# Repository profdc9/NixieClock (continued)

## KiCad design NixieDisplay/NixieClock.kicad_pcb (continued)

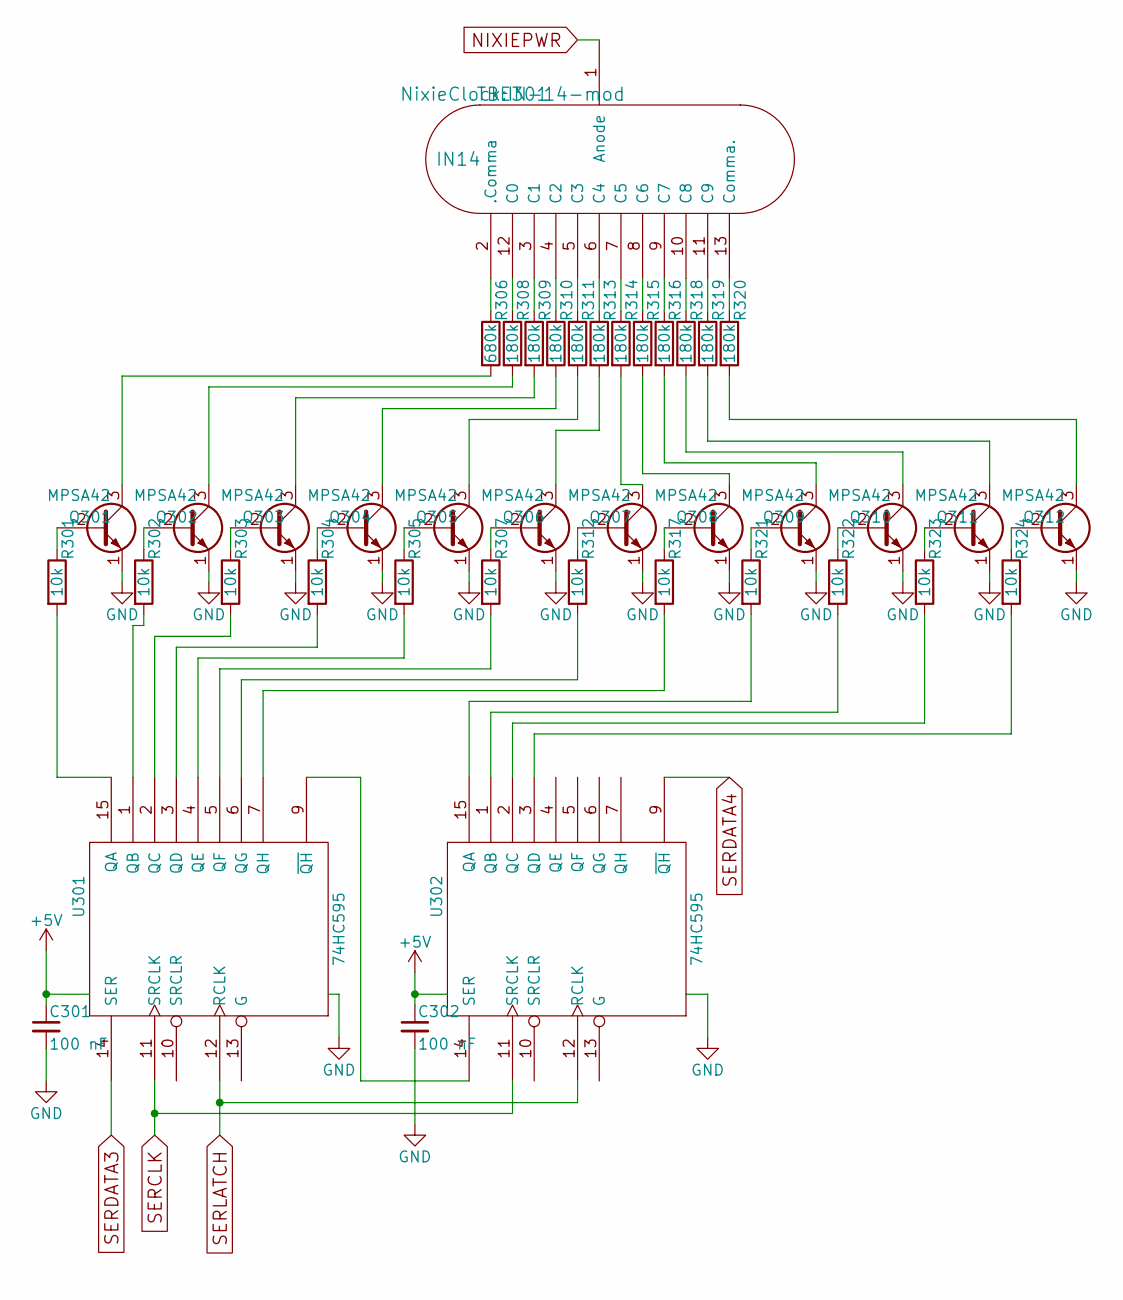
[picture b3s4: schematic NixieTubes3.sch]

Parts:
C301, C302: 100 nF; C_Disc_D5.0mm_W2.5mm_P2.50mm
Q301, Q302, Q303, Q304, Q305, Q306, Q307, Q308, Q309, Q310, Q311, Q312: MPSA42; TO-92_Molded_Narrow
R301, R302, R303, R304, R305, R307, R312, R317, R321, R322, R323, R324: 10k; R_Axial_DIN0207_L6.3mm_D2.5mm_P7.62mm_Horizontal
R306: 680k; R_Axial_DIN0207_L6.3mm_D2.5mm_P7.62mm_Horizontal
R308, R309, R310, R311, R313, R314, R315, R316, R318, R319, R320: 180k; R_Axial_DIN0207_L6.3mm_D2.5mm_P7.62mm_Horizontal
TBE301: IN14; IN-14-mod
U301, U302: 74HC595; DIP-16_W7.62mm_Socket

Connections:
+5V: C301.1, C302.1, U301.16 (VCC), U302.16 (VCC); also elsewhere on the board
GND: C301.2, C302.2, Q301.1 (E), Q302.1 (E), Q303.1 (E), Q304.1 (E), Q305.1 (E), Q306.1 (E), Q307.1 (E), Q308.1 (E), Q309.1 (E), Q310.1 (E), Q311.1 (E), Q312.1 (E), U301.8 (GND), U302.8 (GND); also elsewhere on the board
NIXIEPWR: TBE301.1 (Anode); also elsewhere on the board
unnamed: Q301.2 (B), R301.1
unnamed: Q301.3 (C), R306.2
unnamed: Q302.2 (B), R302.1
unnamed: Q302.3 (C), R308.2
unnamed: Q303.2 (B), R303.1
unnamed: Q303.3 (C), R309.2
unnamed: Q304.2 (B), R304.1
unnamed: Q304.3 (C), R310.2
unnamed: Q305.2 (B), R305.1
unnamed: Q305.3 (C), R311.2
unnamed: Q306.2 (B), R307.1
unnamed: Q306.3 (C), R313.2
unnamed: Q307.2 (B), R312.1
unnamed: Q307.3 (C), R314.2
unnamed: Q308.2 (B), R317.1
unnamed: Q308.3 (C), R315.2
unnamed: Q309.2 (B), R321.1
unnamed: Q309.3 (C), R316.2
unnamed: Q310.2 (B), R322.1
unnamed: Q310.3 (C), R318.2
unnamed: Q311.2 (B), R323.1
unnamed: Q311.3 (C), R319.2
unnamed: Q312.2 (B), R324.1
unnamed: Q312.3 (C), R320.2
unnamed: R301.2, U301.15 (QA)
unnamed: R302.2, U301.1 (QB)
unnamed: R303.2, U301.2 (QC)
unnamed: R304.2, U301.3 (QD)
unnamed: R305.2, U301.4 (QE)
unnamed: R306.1, TBE301.2 (.Comma)
unnamed: R307.2, U301.5 (QF)
unnamed: R308.1, TBE301.12 (C0)
unnamed: R309.1, TBE301.3 (C1)
unnamed: R310.1, TBE301.4 (C2)
unnamed: R311.1, TBE301.5 (C3)
unnamed: R312.2, U301.6 (QG)
unnamed: R313.1, TBE301.6 (C4)
unnamed: R314.1, TBE301.7 (C5)
unnamed: R315.1, TBE301.8 (C6)
unnamed: R316.1, TBE301.9 (C7)
unnamed: R317.2, U301.7 (QH)
unnamed: R318.1, TBE301.10 (C8)
unnamed: R319.1, TBE301.11 (C9)
unnamed: R320.1, TBE301.13 (Comma.)
unnamed: R321.2, U302.15 (QA)
unnamed: R322.2, U302.1 (QB)
unnamed: R323.2, U302.2 (QC)
unnamed: R324.2, U302.3 (QD)
unnamed: U301.9 (~QH), U302.14 (SER)
SERCLK: U301.11 (SRCLK), U302.11 (SRCLK); also elsewhere on the board
SERDATA3: U301.14 (SER); also elsewhere on the board
SERDATA4: U302.9 (~QH); also elsewhere on the board
SERLATCH: U301.12 (RCLK), U302.12 (RCLK); also elsewhere on the board

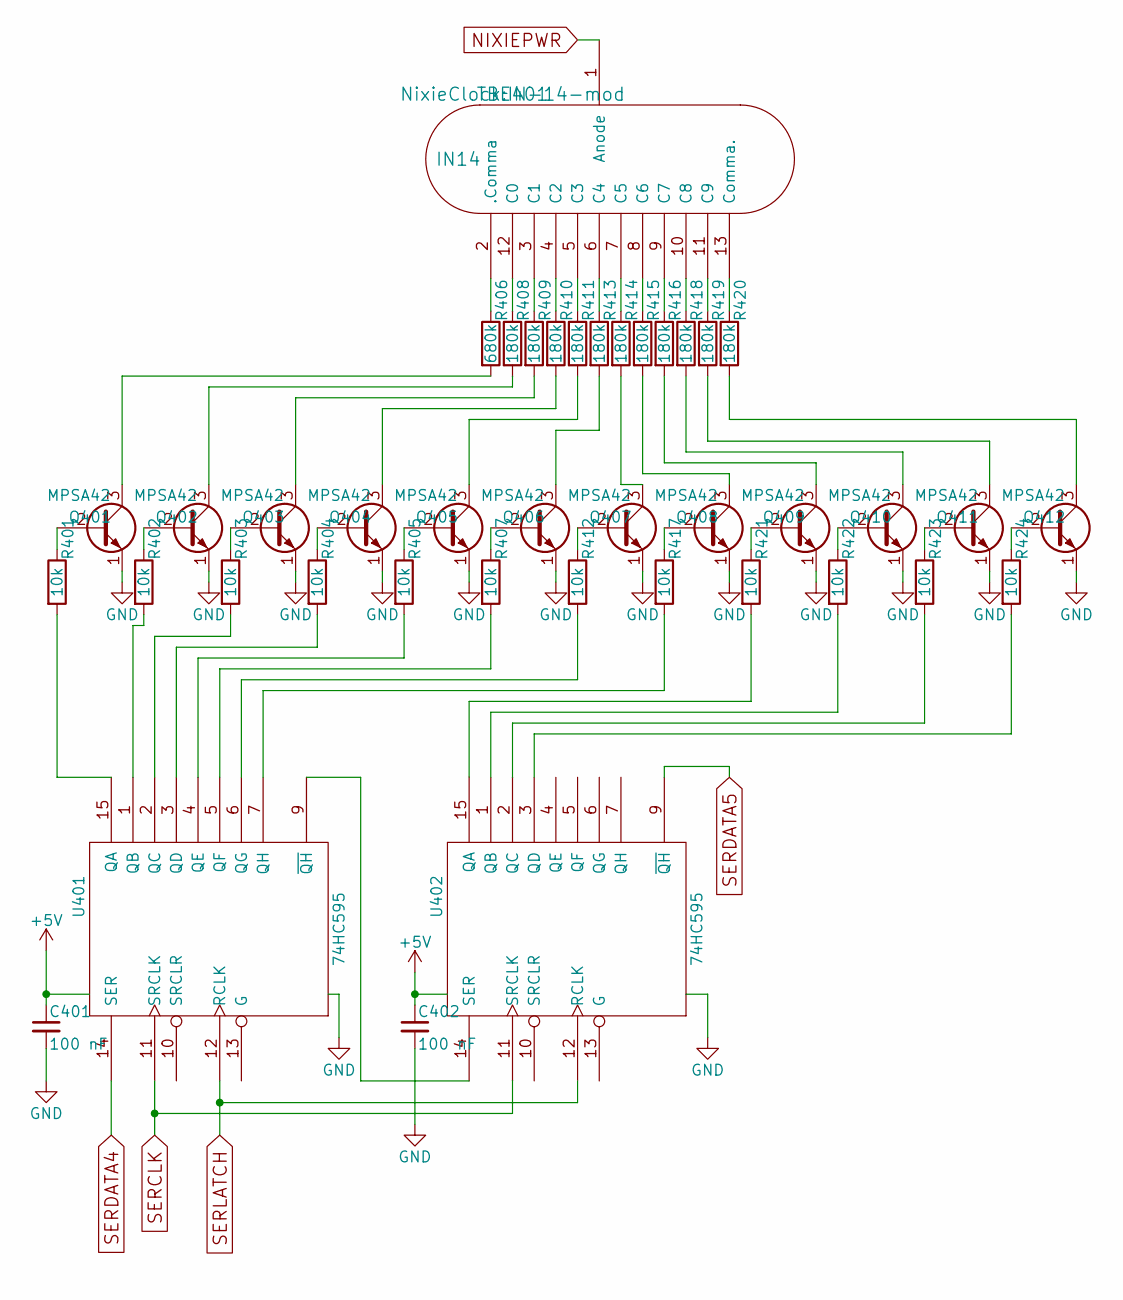
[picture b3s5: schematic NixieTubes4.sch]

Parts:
C401, C402: 100 nF; C_Disc_D5.0mm_W2.5mm_P2.50mm
Q401, Q402, Q403, Q404, Q405, Q406, Q407, Q408, Q409, Q410, Q411, Q412: MPSA42; TO-92_Molded_Narrow
R401, R402, R403, R404, R405, R407, R412, R417, R421, R422, R423, R424: 10k; R_Axial_DIN0207_L6.3mm_D2.5mm_P7.62mm_Horizontal
R406: 680k; R_Axial_DIN0207_L6.3mm_D2.5mm_P7.62mm_Horizontal
R408, R409, R410, R411, R413, R414, R415, R416, R418, R419, R420: 180k; R_Axial_DIN0207_L6.3mm_D2.5mm_P7.62mm_Horizontal
TBE401: IN14; IN-14-mod
U401, U402: 74HC595; DIP-16_W7.62mm_Socket

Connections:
+5V: C401.1, C402.1, U401.16 (VCC), U402.16 (VCC); also elsewhere on the board
GND: C401.2, C402.2, Q401.1 (E), Q402.1 (E), Q403.1 (E), Q404.1 (E), Q405.1 (E), Q406.1 (E), Q407.1 (E), Q408.1 (E), Q409.1 (E), Q410.1 (E), Q411.1 (E), Q412.1 (E), U401.8 (GND), U402.8 (GND); also elsewhere on the board
NIXIEPWR: TBE401.1 (Anode); also elsewhere on the board
unnamed: Q401.2 (B), R401.1
unnamed: Q401.3 (C), R406.2
unnamed: Q402.2 (B), R402.1
unnamed: Q402.3 (C), R408.2
unnamed: Q403.2 (B), R403.1
unnamed: Q403.3 (C), R409.2
unnamed: Q404.2 (B), R404.1
unnamed: Q404.3 (C), R410.2
unnamed: Q405.2 (B), R405.1
unnamed: Q405.3 (C), R411.2
unnamed: Q406.2 (B), R407.1
unnamed: Q406.3 (C), R413.2
unnamed: Q407.2 (B), R412.1
unnamed: Q407.3 (C), R414.2
unnamed: Q408.2 (B), R417.1
unnamed: Q408.3 (C), R415.2
unnamed: Q409.2 (B), R421.1
unnamed: Q409.3 (C), R416.2
unnamed: Q410.2 (B), R422.1
unnamed: Q410.3 (C), R418.2
unnamed: Q411.2 (B), R423.1
unnamed: Q411.3 (C), R419.2
unnamed: Q412.2 (B), R424.1
unnamed: Q412.3 (C), R420.2
unnamed: R401.2, U401.15 (QA)
unnamed: R402.2, U401.1 (QB)
unnamed: R403.2, U401.2 (QC)
unnamed: R404.2, U401.3 (QD)
unnamed: R405.2, U401.4 (QE)
unnamed: R406.1, TBE401.2 (.Comma)
unnamed: R407.2, U401.5 (QF)
unnamed: R408.1, TBE401.12 (C0)
unnamed: R409.1, TBE401.3 (C1)
unnamed: R410.1, TBE401.4 (C2)
unnamed: R411.1, TBE401.5 (C3)
unnamed: R412.2, U401.6 (QG)
unnamed: R413.1, TBE401.6 (C4)
unnamed: R414.1, TBE401.7 (C5)
unnamed: R415.1, TBE401.8 (C6)
unnamed: R416.1, TBE401.9 (C7)
unnamed: R417.2, U401.7 (QH)
unnamed: R418.1, TBE401.10 (C8)
unnamed: R419.1, TBE401.11 (C9)
unnamed: R420.1, TBE401.13 (Comma.)
unnamed: R421.2, U402.15 (QA)
unnamed: R422.2, U402.1 (QB)
unnamed: R423.2, U402.2 (QC)
unnamed: R424.2, U402.3 (QD)
unnamed: U401.9 (~QH), U402.14 (SER)
SERCLK: U401.11 (SRCLK), U402.11 (SRCLK); also elsewhere on the board
SERDATA4: U401.14 (SER); also elsewhere on the board
SERDATA5: U402.9 (~QH); also elsewhere on the board
SERLATCH: U401.12 (RCLK), U402.12 (RCLK); also elsewhere on the board

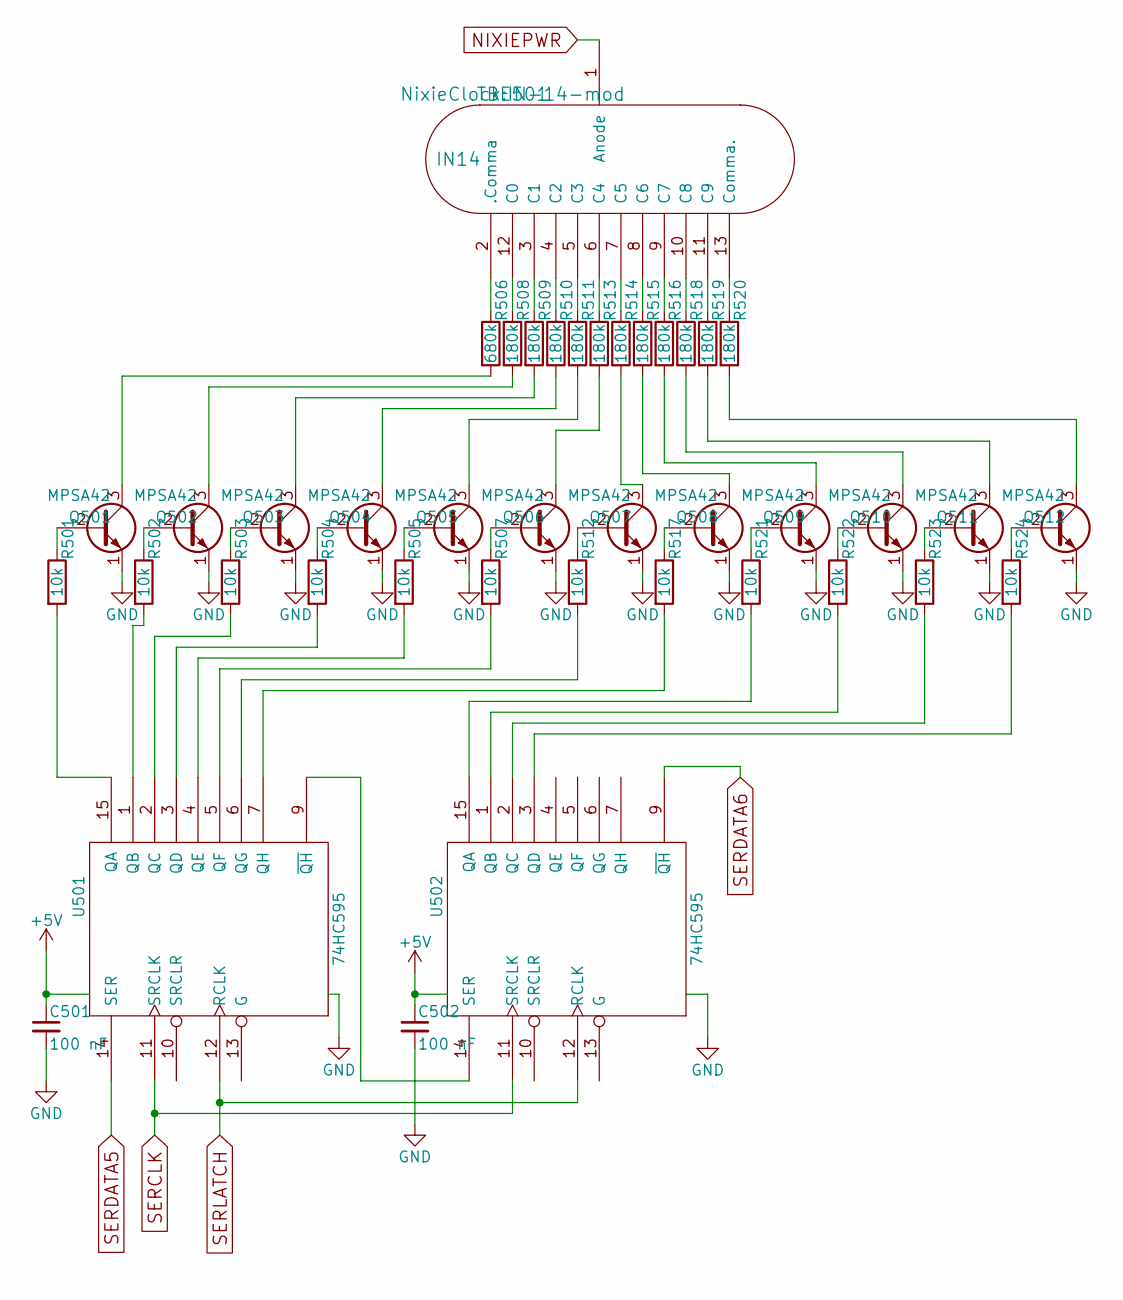
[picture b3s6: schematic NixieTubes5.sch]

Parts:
C501, C502: 100 nF; C_Disc_D5.0mm_W2.5mm_P2.50mm
Q501, Q502, Q503, Q504, Q505, Q506, Q507, Q508, Q509, Q510, Q511, Q512: MPSA42; TO-92_Molded_Narrow
R501, R502, R503, R504, R505, R507, R512, R517, R521, R522, R523, R524: 10k; R_Axial_DIN0207_L6.3mm_D2.5mm_P7.62mm_Horizontal
R506: 680k; R_Axial_DIN0207_L6.3mm_D2.5mm_P7.62mm_Horizontal
R508, R509, R510, R511, R513, R514, R515, R516, R518, R519, R520: 180k; R_Axial_DIN0207_L6.3mm_D2.5mm_P7.62mm_Horizontal
TBE501: IN14; IN-14-mod
U501, U502: 74HC595; DIP-16_W7.62mm_Socket

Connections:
+5V: C501.1, C502.1, U501.16 (VCC), U502.16 (VCC); also elsewhere on the board
GND: C501.2, C502.2, Q501.1 (E), Q502.1 (E), Q503.1 (E), Q504.1 (E), Q505.1 (E), Q506.1 (E), Q507.1 (E), Q508.1 (E), Q509.1 (E), Q510.1 (E), Q511.1 (E), Q512.1 (E), U501.8 (GND), U502.8 (GND); also elsewhere on the board
NIXIEPWR: TBE501.1 (Anode); also elsewhere on the board
unnamed: Q501.2 (B), R501.1
unnamed: Q501.3 (C), R506.2
unnamed: Q502.2 (B), R502.1
unnamed: Q502.3 (C), R508.2
unnamed: Q503.2 (B), R503.1
unnamed: Q503.3 (C), R509.2
unnamed: Q504.2 (B), R504.1
unnamed: Q504.3 (C), R510.2
unnamed: Q505.2 (B), R505.1
unnamed: Q505.3 (C), R511.2
unnamed: Q506.2 (B), R507.1
unnamed: Q506.3 (C), R513.2
unnamed: Q507.2 (B), R512.1
unnamed: Q507.3 (C), R514.2
unnamed: Q508.2 (B), R517.1
unnamed: Q508.3 (C), R515.2
unnamed: Q509.2 (B), R521.1
unnamed: Q509.3 (C), R516.2
unnamed: Q510.2 (B), R522.1
unnamed: Q510.3 (C), R518.2
unnamed: Q511.2 (B), R523.1
unnamed: Q511.3 (C), R519.2
unnamed: Q512.2 (B), R524.1
unnamed: Q512.3 (C), R520.2
unnamed: R501.2, U501.15 (QA)
unnamed: R502.2, U501.1 (QB)
unnamed: R503.2, U501.2 (QC)
unnamed: R504.2, U501.3 (QD)
unnamed: R505.2, U501.4 (QE)
unnamed: R506.1, TBE501.2 (.Comma)
unnamed: R507.2, U501.5 (QF)
unnamed: R508.1, TBE501.12 (C0)
unnamed: R509.1, TBE501.3 (C1)
unnamed: R510.1, TBE501.4 (C2)
unnamed: R511.1, TBE501.5 (C3)
unnamed: R512.2, U501.6 (QG)
unnamed: R513.1, TBE501.6 (C4)
unnamed: R514.1, TBE501.7 (C5)
unnamed: R515.1, TBE501.8 (C6)
unnamed: R516.1, TBE501.9 (C7)
unnamed: R517.2, U501.7 (QH)
unnamed: R518.1, TBE501.10 (C8)
unnamed: R519.1, TBE501.11 (C9)
unnamed: R520.1, TBE501.13 (Comma.)
unnamed: R521.2, U502.15 (QA)
unnamed: R522.2, U502.1 (QB)
unnamed: R523.2, U502.2 (QC)
unnamed: R524.2, U502.3 (QD)
unnamed: U501.9 (~QH), U502.14 (SER)
SERCLK: U501.11 (SRCLK), U502.11 (SRCLK); also elsewhere on the board
SERDATA5: U501.14 (SER); also elsewhere on the board
SERDATA6: U502.9 (~QH); also elsewhere on the board
SERLATCH: U501.12 (RCLK), U502.12 (RCLK); also elsewhere on the board

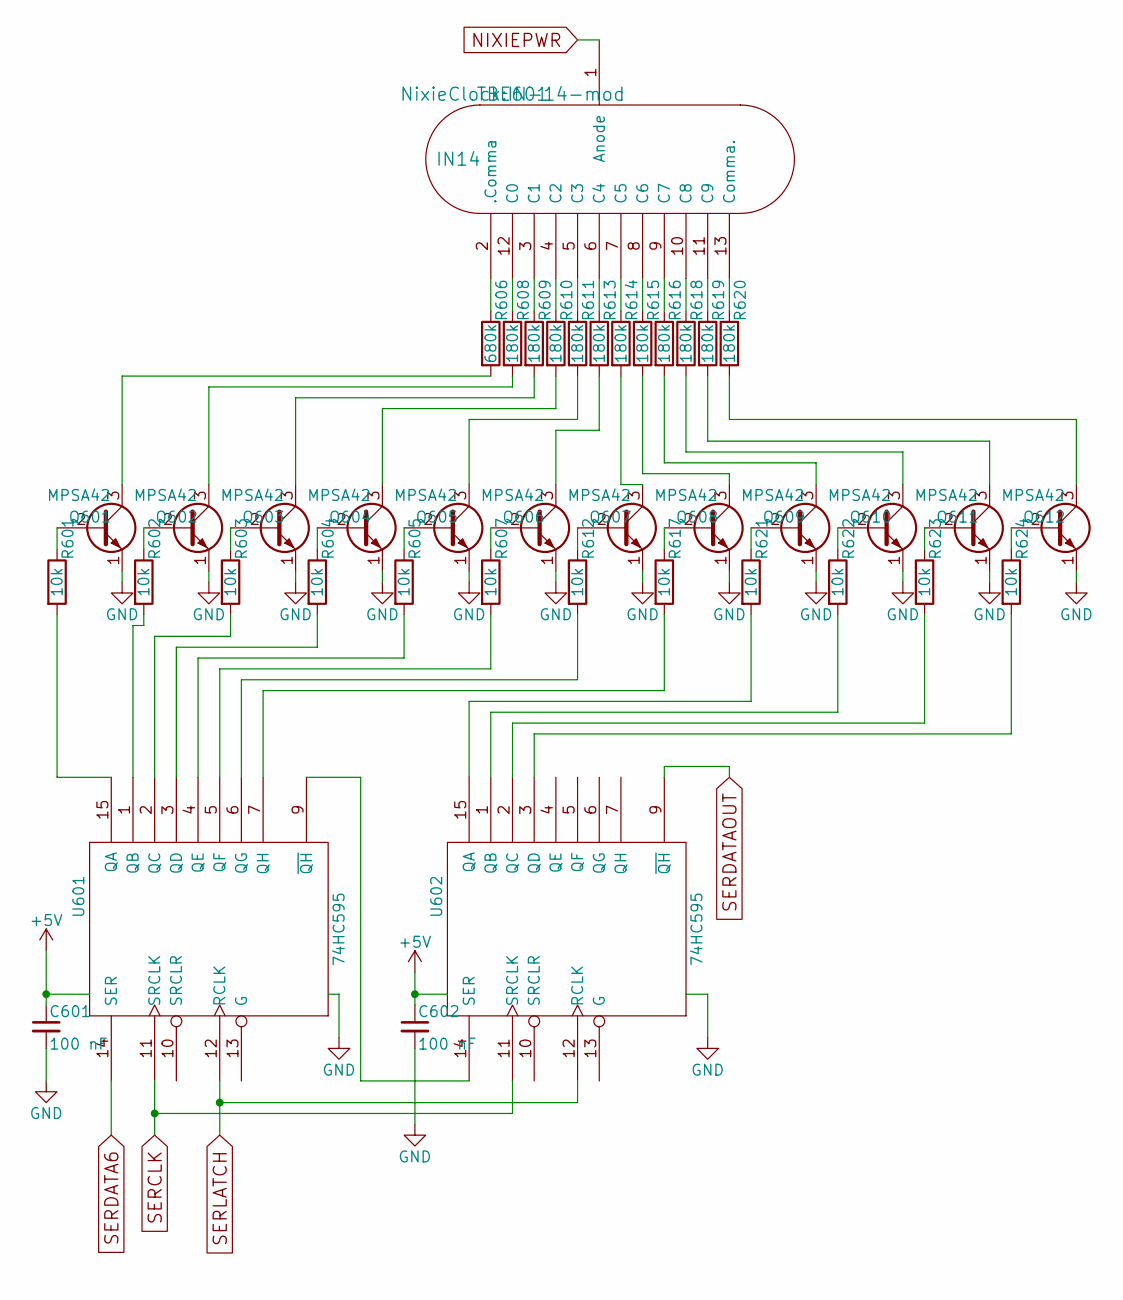
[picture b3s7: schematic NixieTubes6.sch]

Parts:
C601, C602: 100 nF; C_Disc_D5.0mm_W2.5mm_P2.50mm
Q601, Q602, Q603, Q604, Q605, Q606, Q607, Q608, Q609, Q610, Q611, Q612: MPSA42; TO-92_Molded_Narrow
R601, R602, R603, R604, R605, R607, R612, R617, R621, R622, R623, R624: 10k; R_Axial_DIN0207_L6.3mm_D2.5mm_P7.62mm_Horizontal
R606: 680k; R_Axial_DIN0207_L6.3mm_D2.5mm_P7.62mm_Horizontal
R608, R609, R610, R611, R613, R614, R615, R616, R618, R619, R620: 180k; R_Axial_DIN0207_L6.3mm_D2.5mm_P7.62mm_Horizontal
TBE601: IN14; IN-14-mod
U601, U602: 74HC595; DIP-16_W7.62mm_Socket

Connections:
+5V: C601.1, C602.1, U601.16 (VCC), U602.16 (VCC); also elsewhere on the board
GND: C601.2, C602.2, Q601.1 (E), Q602.1 (E), Q603.1 (E), Q604.1 (E), Q605.1 (E), Q606.1 (E), Q607.1 (E), Q608.1 (E), Q609.1 (E), Q610.1 (E), Q611.1 (E), Q612.1 (E), U601.8 (GND), U602.8 (GND); also elsewhere on the board
NIXIEPWR: TBE601.1 (Anode); also elsewhere on the board
unnamed: Q601.2 (B), R601.1
unnamed: Q601.3 (C), R606.2
unnamed: Q602.2 (B), R602.1
unnamed: Q602.3 (C), R608.2
unnamed: Q603.2 (B), R603.1
unnamed: Q603.3 (C), R609.2
unnamed: Q604.2 (B), R604.1
unnamed: Q604.3 (C), R610.2
unnamed: Q605.2 (B), R605.1
unnamed: Q605.3 (C), R611.2
unnamed: Q606.2 (B), R607.1
unnamed: Q606.3 (C), R613.2
unnamed: Q607.2 (B), R612.1
unnamed: Q607.3 (C), R614.2
unnamed: Q608.2 (B), R617.1
unnamed: Q608.3 (C), R615.2
unnamed: Q609.2 (B), R621.1
unnamed: Q609.3 (C), R616.2
unnamed: Q610.2 (B), R622.1
unnamed: Q610.3 (C), R618.2
unnamed: Q611.2 (B), R623.1
unnamed: Q611.3 (C), R619.2
unnamed: Q612.2 (B), R624.1
unnamed: Q612.3 (C), R620.2
unnamed: R601.2, U601.15 (QA)
unnamed: R602.2, U601.1 (QB)
unnamed: R603.2, U601.2 (QC)
unnamed: R604.2, U601.3 (QD)
unnamed: R605.2, U601.4 (QE)
unnamed: R606.1, TBE601.2 (.Comma)
unnamed: R607.2, U601.5 (QF)
unnamed: R608.1, TBE601.12 (C0)
unnamed: R609.1, TBE601.3 (C1)
unnamed: R610.1, TBE601.4 (C2)
unnamed: R611.1, TBE601.5 (C3)
unnamed: R612.2, U601.6 (QG)
unnamed: R613.1, TBE601.6 (C4)
unnamed: R614.1, TBE601.7 (C5)
unnamed: R615.1, TBE601.8 (C6)
unnamed: R616.1, TBE601.9 (C7)
unnamed: R617.2, U601.7 (QH)
unnamed: R618.1, TBE601.10 (C8)
unnamed: R619.1, TBE601.11 (C9)
unnamed: R620.1, TBE601.13 (Comma.)
unnamed: R621.2, U602.15 (QA)
unnamed: R622.2, U602.1 (QB)
unnamed: R623.2, U602.2 (QC)
unnamed: R624.2, U602.3 (QD)
unnamed: U601.9 (~QH), U602.14 (SER)
SERCLK: U601.11 (SRCLK), U602.11 (SRCLK); also elsewhere on the board
SERDATA6: U601.14 (SER); also elsewhere on the board
SERDATAOUT: U602.9 (~QH); also elsewhere on the board
SERLATCH: U601.12 (RCLK), U602.12 (RCLK); also elsewhere on the board

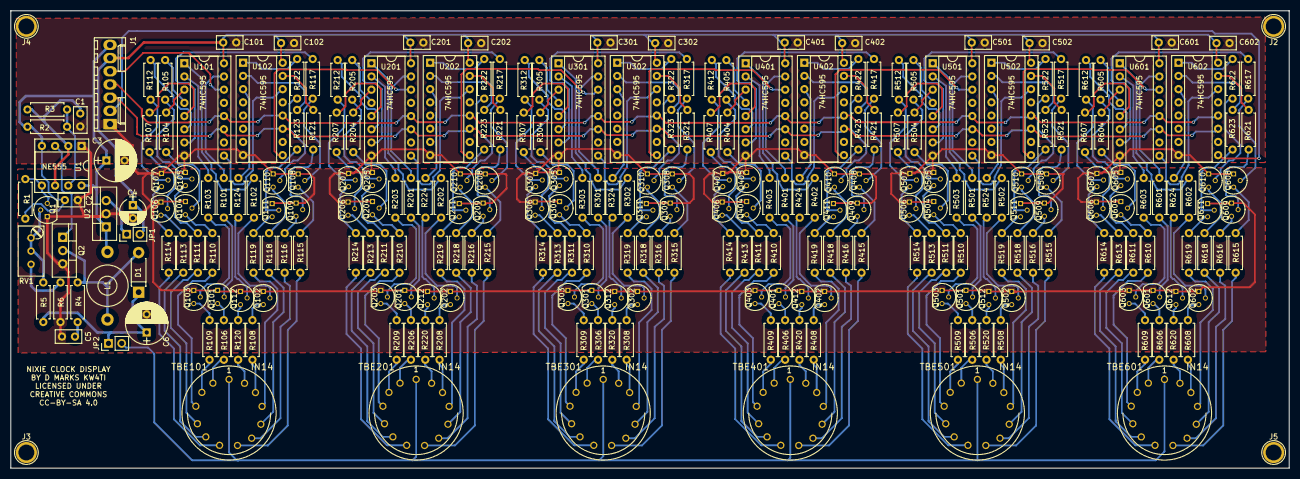
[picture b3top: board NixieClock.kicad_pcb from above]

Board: 2 copper layers, 246.0 x 88.0 mm, 272 parts (0 on the bottom side), 317 nets.

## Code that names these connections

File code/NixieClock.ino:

/*  NixieClock.ino */

/*
 * Copyright (c) 2020 Daniel Marks

This software is provided 'as-is', without any express or implied
warranty. In no event will the authors be held liable for any damages
arising from the use of this software.

Permission is granted to anyone to use this software for any purpose,
including commercial applications, and to alter it and redistribute it
freely, subject to the following restrictions:

1. The origin of this software must not be misrepresented; you must not
   claim that you wrote the original software. If you use this software
   in a product, an acknowledgment in the product documentation would be
   appreciated but is not required.
2. Altered source versions must be plainly marked as such, and must not be
   misrepresented as being the original software.
3. This notice may not be removed or altered from any source distribution.
 */

 #define DHT_SENSOR

#include <Arduino.h>
#include <SPI.h>
#include <Wire.h>
#include <EEPROM.h>
#include <DS3231.h>

#ifdef DHT_SENSOR
#include <DHT.h>
#endif

#define SERIAL_LATCH 10
#define SERIAL_DATA 11
#define SERIAL_DATAOUT 12
#define SERIAL_CLK 13
#define BUTTON1 14
#define BUTTON2 15
#define BUTTON3 16

#define ARDUINORX 1
#define ARDUINOTX 0

#define I2C_SDA 4
#define I2C_SCL 5

#define LED1 3
#define LED2 5
#define LED3 6

#define EEPROM_1224HR 0
#define EEPROM_TEMPCF 1

SPISettings spiA(4000000, MSBFIRST, SPI_MODE0);

#define NUM_DIGITS 6

const byte digit_code[] =   { 0x01, 0x02, 0x04, 0x08, 0x10, 0x20 };
const byte number1_code[] = { 0x00, 0x04, 0x08, 0x10, 0x20, 0x40, 0x80, 0x01, 0x00, 0x00, 0x02, 0x00, 0x00 };
const byte number2_code[] = { 0x04, 0x00, 0x00, 0x00, 0x00, 0x00, 0x00, 0x00, 0x01, 0x02, 0x00, 0x08, 0x00 };

const byte ticks1_code[] = { 0x00, 0x00, 0x02, 0x02 };
const byte ticks2_code[] = { 0x00, 0x08, 0x00, 0x08 };

volatile byte digits[NUM_DIGITS];
volatile byte ticks[NUM_DIGITS];
byte displayrefreshcycles;
byte current_digit;
byte hour12;
byte tempcf;
DS3231 Clock;
#ifdef DHT_SENSOR
DHT DHTSensor(4, DHT22, 1);
#endif

#define NUM_BUTTONS 3

const byte buttonPin[NUM_BUTTONS] = {BUTTON1, BUTTON2, BUTTON3};
static byte constStateButton[NUM_BUTTONS];
volatile byte curStateButton[NUM_BUTTONS];
volatile bool pushedButton[NUM_BUTTONS];

void write_led_state(byte d1, byte d2, byte d3)
{
  analogWrite(LED1,d1);
  analogWrite(LED2,d2);
  analogWrite(LED3,d3);
}

bool isButtonDown(byte b)
{
  return !curStateButton[b];
}

void waitButtonUp(byte b)
{
  while (curStateButton[b] == LOW);
  pushedButton[b] = false;
}

bool getPushedButton(byte b)
{
  if (pushedButton[b])
  {
    pushedButton[b] = false;
    return true;
  }
  return false;
}

void debounce_buttons(void)
{
  for (byte b = 0; b < NUM_BUTTONS; b++)
  {
    byte state = digitalRead(buttonPin[b]);
    if (curStateButton[b] != state)
    {
      if ((++constStateButton[b]) >= 50)
      {
        curStateButton[b] = state;
        if (state == LOW) pushedButton[b] = true;
        constStateButton[b] = 0;
      }
    } else constStateButton[b] = 0;
  }
}

ISR(TIMER1_COMPA_vect)
{
  SPI.beginTransaction(spiA);
  if (displayrefreshcycles > 0)
  {
    displayrefreshcycles--;
    SPI.transfer(digit_code[current_digit]);
    SPI.transfer(number2_code[digits[current_digit]] | ticks2_code[ticks[current_digit]] );
    SPI.transfer(number1_code[digits[current_digit]] | ticks1_code[ticks[current_digit]] );
  }
  else
  {
    displayrefreshcycles = 4;
    SPI.transfer(0);
    SPI.transfer(0);
    SPI.transfer(0);
    if ((++current_digit) >= NUM_DIGITS)
      current_digit = 0;
  }
  SPI.endTransaction();
  digitalWrite(SERIAL_LATCH, LOW);
  debounce_buttons();
  digitalWrite(SERIAL_LATCH, HIGH);
}

void setup() {
  current_digit = 0;
  pinMode(SERIAL_LATCH, OUTPUT);
  pinMode(LED1, OUTPUT);
  digitalWrite(LED1, LOW);
  pinMode(LED2, OUTPUT);
  digitalWrite(LED2, LOW);
  pinMode(LED3, OUTPUT);
  digitalWrite(LED3, LOW);
  pinMode(BUTTON1, INPUT);
  pinMode(BUTTON2, INPUT);
  pinMode(BUTTON3, INPUT);
  SPI.begin();

  noInterrupts();           // disable all interrupts
  TCCR1A = 0;
  TCCR1B = 0;
  TCNT1  = 0;
  OCR1A = 16;            // compare match register 16MHz/256/2Hz
  TCCR1B |= (1 << WGM12);   // CTC mode
  TCCR1B |= ((1 << CS11) | (1 << CS10));    // 256 prescaler
  TIMSK1 |= (1 << OCIE1A);  // enable timer compare interrupt
  interrupts();             // enable all interrupts

  Serial.begin(9600);
  Wire.begin();
  Clock.setClockMode(false);
  hour12 = (EEPROM.read(EEPROM_1224HR) == 1) ? 1 : 0;
  tempcf = (EEPROM.read(EEPROM_TEMPCF) == 1) ? 1 : 0;
#ifdef DHT_SENSOR
  DHTSensor.begin();
#endif
}

void display_1_number(byte ind, byte b)
{
  digits[ind] = b / 10;
  digits[ind + 1] = b % 10;
}

void display_three_numbers(byte n1, byte n2, byte n3)
{
  display_1_number(0, n1);
  display_1_number(2, n2);
  display_1_number(4, n3);
}

void display_current_time(void)
{
  bool h12, PM;
  byte nowHour = Clock.getHour(h12, PM);
  if (hour12)
  {
    if ((nowHour >= 12) && (nowHour <= 23)) ticks[0] = ticks[1] = 1;
    if (nowHour > 12) nowHour -= 12;
    if (nowHour == 0) nowHour = 12;
  }
  display_three_numbers(nowHour, Clock.getMinute(), Clock.getSecond());
}

void display_current_date(void)
{
  bool Century;
  display_three_numbers(Clock.getYear(), Clock.getMonth(Century), Clock.getDate());
}

void set_digs(byte *v, byte val)
{
  for (byte i = 0; i < NUM_DIGITS; i++) v[i] = val;
}

void clear_display(void)
{
  set_digs(digits, 12);
}

void clear_ticks(void)
{
  set_digs(ticks, 0);
}

void all_ticks(void)
{
  set_digs(ticks, 3);
}

unsigned short getNewNumber(unsigned short n, byte dig, byte ndig, unsigned short minval, unsigned short maxval)
{
  clear_ticks();
  for (;;)
  {
    unsigned short v = n;
    for (byte i = ndig; i > 0;)
    {
      i--;
      digits[dig + i] = v % 10;
      ticks[dig + i] = 3;
      v = v / 10;
    }
    if (getPushedButton(2))
    {
      if (n > minval) n--;
      else n = maxval;
    } else if (getPushedButton(1))
    {
      if (n < maxval) n++;
      else n = minval;
    } else if (getPushedButton(0))
      break;
  }
  return n;
}

void set_time_and_date(void)
{
  bool h12, PM, Century;
  clear_display();
  delay(500);
  hour12 = getNewNumber(hour12, 0, 1, 0, 1);
  EEPROM.write(EEPROM_1224HR, hour12);
#ifdef DHT_SENSOR
  clear_display();
  tempcf = getNewNumber(tempcf, 1, 2, 0, 1);
  EEPROM.write(EEPROM_TEMPCF, tempcf);
#endif
  display_three_numbers(Clock.getYear(), Clock.getMonth(Century), Clock.getDate());
  byte newYear = getNewNumber(Clock.getYear(), 0, 2, 0, 99);
  byte newMonth = getNewNumber(Clock.getMonth(Century), 2, 2, 1, 12);
  byte newDate = getNewNumber(Clock.getDate(), 4, 2, 1, 31);
  display_current_time();
  byte newHour = Clock.getHour(h12, PM);
  newHour = getNewNumber(newHour, 0, 2, 0, 23);
  byte newMinute = getNewNumber(Clock.getMinute(), 2, 2, 0, 59);
  byte newSecond = getNewNumber(Clock.getSecond(), 4, 2, 0, 59);
  Clock.setYear(newYear);
  Clock.setMonth(newMonth);
  Clock.setDate(newDate);
  Clock.setHour(newHour);
  Clock.setMinute(newMinute);
  Clock.setSecond(newSecond);
  all_ticks();
  delay(1000);
}

void cathode_condition()
{
  clear_ticks();
  for (byte i = 0; i < 12; i++)
  {
    set_digs(digits, i);
    for (byte j = 0; j < 240; j++)
    {
      delay(250);
      if (getPushedButton(0)) break;
      if (getPushedButton(2)) return;
    }
  }
}

#ifdef DHT_SENSOR
void display_dht(void)
{
  // Reading temperature or humidity takes about 250 milliseconds!
  // Sensor readings may also be up to 2 seconds 'old' (its a very slow sensor)
  float h = DHTSensor.readHumidity();
  float f = DHTSensor.readTemperature(tempcf ? true : false);

  digits[0] = ((byte)f)/10;
  digits[1] = ((byte)f)%10;
  digits[2] = ((byte)(f*10.0f))%10;
  ticks[1] = 1;
  digits[3] = 12;
  digits[4] = ((byte)h)/10;
  digits[5] = ((byte)h)%10;
}
#endif

byte mainlooptick;
byte programtick;
byte cathodetick;

#ifdef DHT_SENSOR
#define TICK_CENTRAL_LOOP 297
#else
#define TICK_CENTRAL_LOOP 247
#endif

void loop() {
  delay(100);
  if ((++mainlooptick) > TICK_CENTRAL_LOOP) mainlooptick = 0;
  if (mainlooptick < 150)
  {
    clear_ticks();
    write_led_state(0,0,255);
    display_current_time();
  } else
#ifdef DHT_SENSOR
  if (mainlooptick < 237)
  {
    clear_ticks();
    write_led_state(0,255,0);
    display_dht();
  } else
#endif
  {
    clear_ticks();
    write_led_state(255,0,0);
    display_current_date();
    ticks[0] = ticks[2] = ticks[4] = 2;
    ticks[1] = ticks[3] = ticks[5] = 1;
  }
  if (isButtonDown(2))
  {
    write_led_state(0,0,0);
    if ((++programtick) >= 20)
    {
      programtick = 0;
      waitButtonUp(2);
      set_time_and_date();
    }
  } else programtick = 0;
  if (isButtonDown(1))
  {
    write_led_state(0,0,0);
    if ((++cathodetick) >= 20)
    {
      cathodetick = 0;
      waitButtonUp(1);
      cathode_condition();
    }
  } else cathodetick = 0;
}

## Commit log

2019-12-31 Added a scanning PCB, much smaller
2020-01-02 First commit of the Nixie Controller
2020-01-03 Placed connectors to make boards stackable
2020-03-02 First usable version of Nixie Tube Clock
2020-03-27 Added speaker output
2020-06-15 Changed connector between boards to 10 pin IDC, added Bill of Materials
2020-10-23 Added capacitors to buttons to filter noise
2021-09-26 Add nixie tube lead alignment tool
2021-09-26 Fixed slight error in schematic
2021-09-30 Add simple clock enclosure CAD files
2021-10-01 Improved enclosure
2021-10-10 Add (unfinished) code comment
